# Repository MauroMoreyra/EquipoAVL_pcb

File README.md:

# EquipoAVL_pcb - vRaptor

## Guía rápida para manejo de versiones

- Habilitar modulo GitFlow en GitKraken.
- Creación de nueva versión: estando posicionado en rama "develop" o "master", GitFlow > Start Release > Nombre "vX.X" (número de versión).
- Finalización de nueva versión: GitFlow > Finish release, tildando "Delete branch". De esta forma se vuelcan a las ramas "develop" y "master" los cambios de la versión del release. A su vez se genera un TAG con el nombre del release "vX.X", que quedará de referencia histórica para futura consulta.

## Mejoras pendientes (previa validación) - vRaptor v1.2

- PCB 4 capas.
- Componentes en ambas caras.
- Revisar tamaño huellas, encapsulados.
- Modificar huellas para que posean el área que las delimita, así se valida el ERC en forma integral (con todos los checks activados).
- Ver otros errores del ERC integral.
- Verificar diseño 1.1 y corregir errores en caso de que existan.
- Verificar margenes tolerados por fabricantes, con el fin de achicar tamaños pistas y separación entre las mismas.
- Agregar información a componentes (desde esquemático).
- Poner conector DB15 en PCB, para utilizar así un cable VGA-DB15 directamente hacia la consola. Revisar tema gabinete.
- Capacitor C504 modificar para que sea de menor tamaño, reducir capacidad? low profile? investigar. Es muy alto (25mm).
- Revisar margenes laterales por tema gabinete - guia para su inserción. Revisar componentes situados muy sobre los bordes.
- Footprints IPC compatible: Revisar normativa IPC 7351 referente a los footprints recomendados de los componentes, ya que no es aconsejable utilizar los footprints recomendados por los fabricantes de las partes (se puede observar que para un mismo encapsulado, distintos fabricantes recomiendan footprints distintos, aunque varíen muy levemente). Revisar generador de footprints que sigue normativa IPC: https://www.pcblibraries.com/ a través del Library Expert.
- Footprints IPC compatible: Revisar densidad de componentes. Esto define el keepout del footprint, o sea, la distancia minima de separación con otro componente. Se recomienda usar una densidad "Normal" según el Library Expert.
- Revisar Bottom Paste de componentes de potencia (ej: LD1085), ya que IPC recomienda una "huella" de pasta de estaño con características especiales (tipo grilla, vías o microvías de disipación en cierta ubicación, etc.).

## Historial de versiones

**Versión 1.1**
- [Referencias de diseño](https://github.com/MauroMoreyra/EquipoAVL_pcb/blob/release/vRaptor-v1.1/Referencias%20de%20dise%C3%B1o%20v1.1.md).
- Se corrige el acceso de las pistas a los pads de los componentes, ahora lo hacen a 90° (no en diagonal). También, en caso de que a un pad entre y salga una pista, ahora ambas lo hacen con el mismo grosor (regla de diseño: ancho pista menor ancho pad, ya que facilita así el soldado de los componentes al no haber tanta transferencia térmica sobre las pistas).
- Se redimensiona el ancho de pistas, muchas se angostaron.
- Se modifican huellas de componentes QFN (```MPU-6050``` y ```NAU8814```), ahora tienen pads más largos (1.5mm) para facilitar el soldado manual (ese es el ancho de la    superficie del pad que la punta del soldador debe hacer contacto -punta ```900m-t-2c``` preferentemente).
- Se agrega tira de pines sobre conexiones de ```MPU-6050``` para tener como alternativa la posiblidad de colocar placa arduino de ese componente (inserción más fácil).

**Versión 1.0**
- Primera versión, entregable de materia Diseño de PCB.

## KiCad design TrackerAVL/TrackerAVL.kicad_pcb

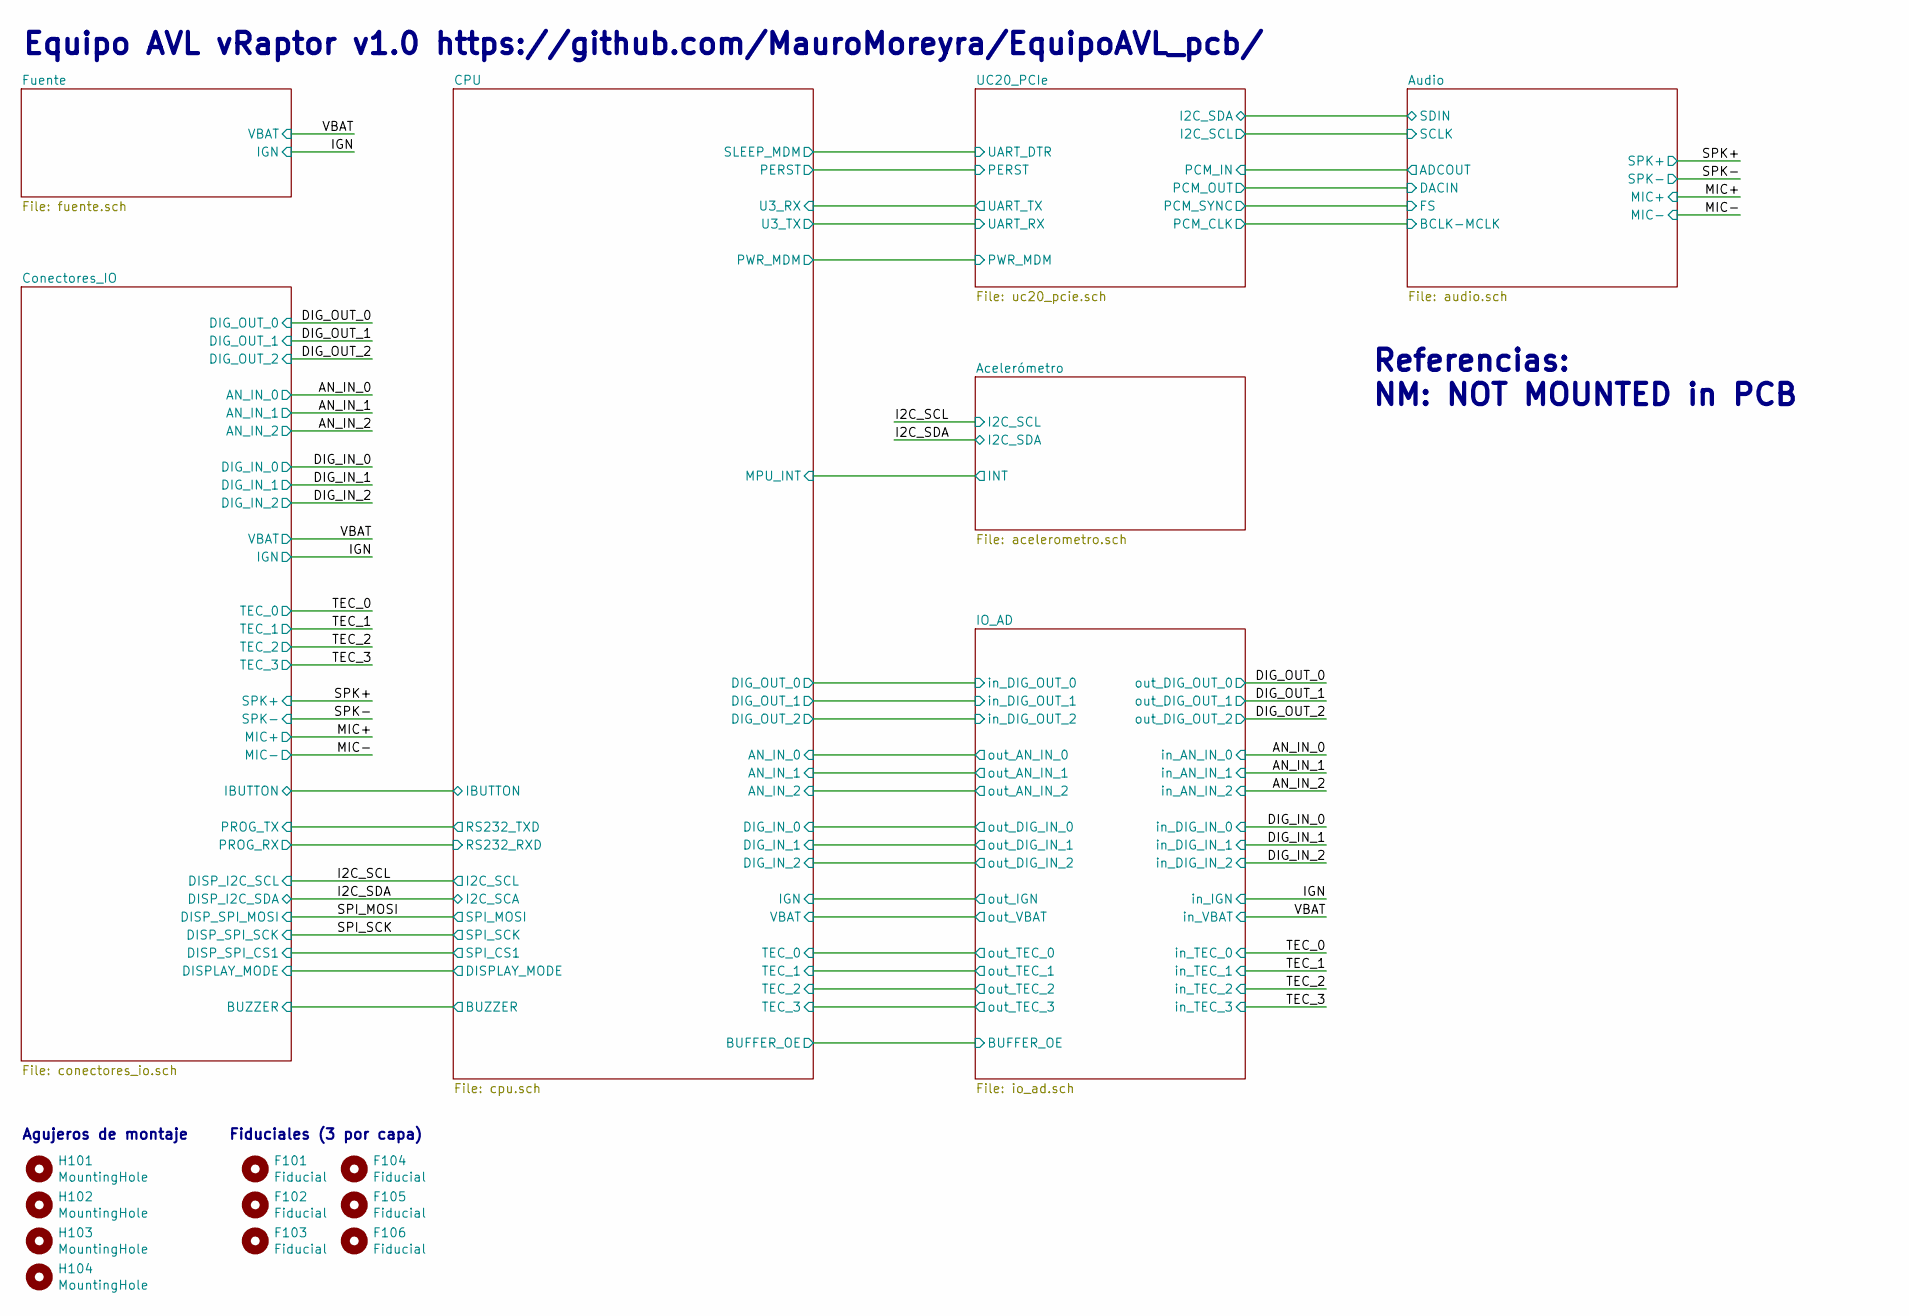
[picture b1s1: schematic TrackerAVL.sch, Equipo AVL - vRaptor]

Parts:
F101, F102, F103, F104, F105, F106: Fiducial; Fiducial_1mm_Dia_2mm_Outer
H101, H102, H103, H104: MountingHole; MountingHole_3.2mm_M3_Pad_Thin

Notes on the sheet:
Equipo AVL vRaptor v1.0 https://github.com/MauroMoreyra/EquipoAVL_pcb/
Referencias: NM: NOT MOUNTED in PCB
Agujeros de montaje
Fiduciales (3 por capa)

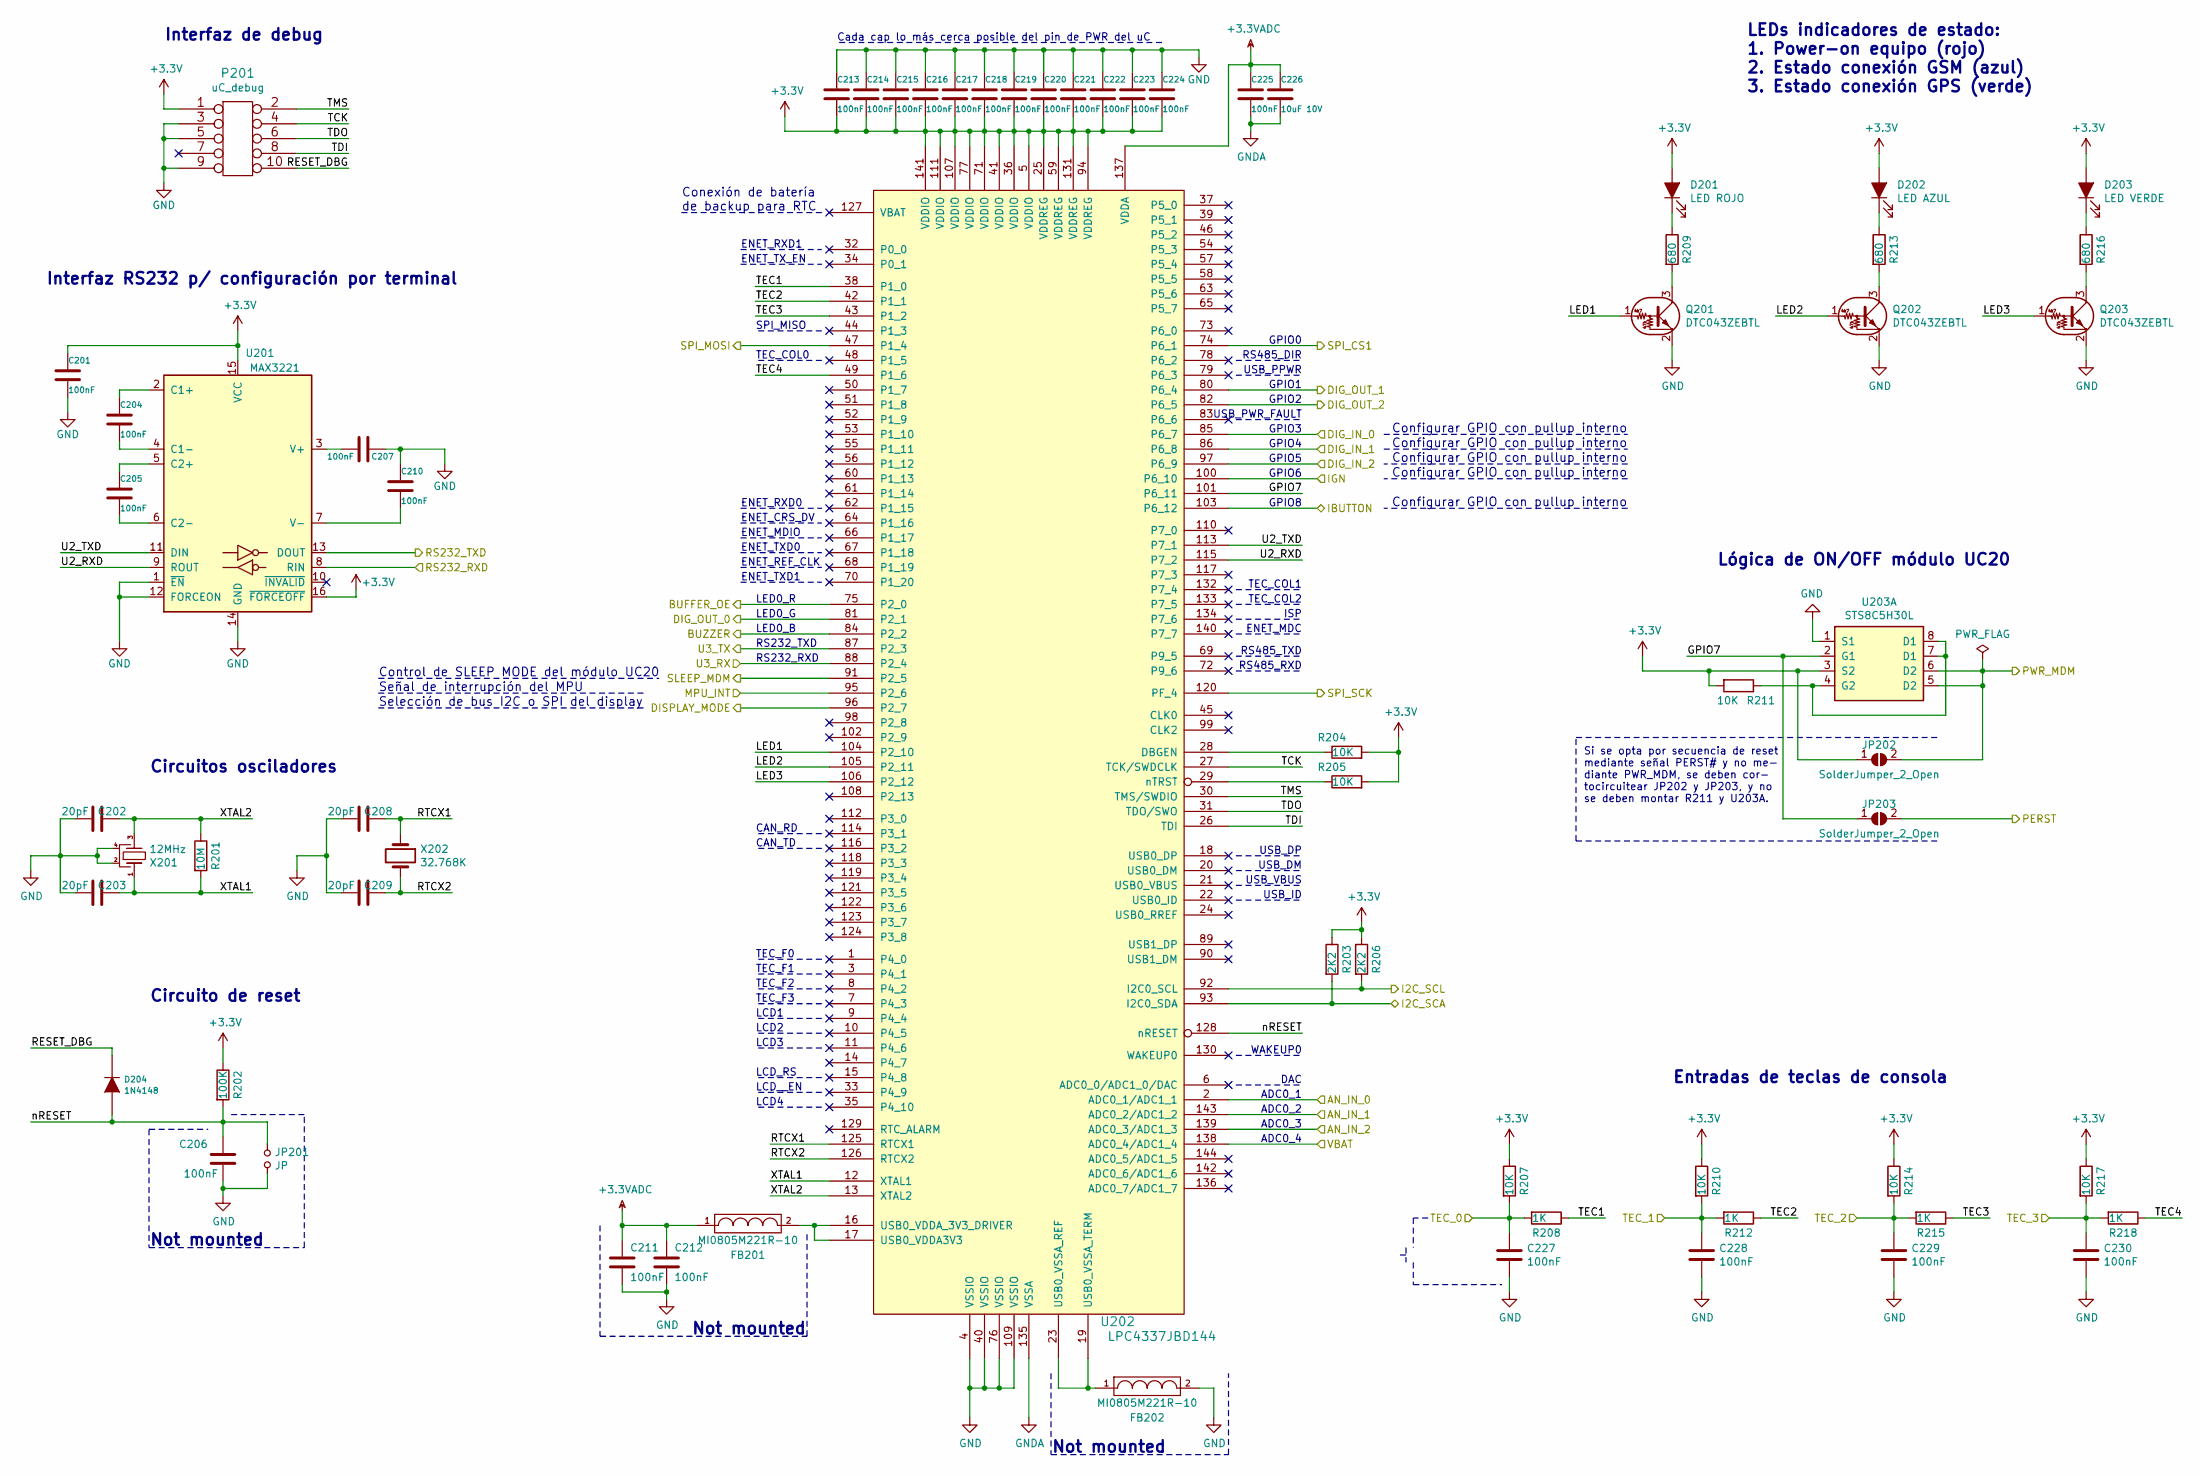
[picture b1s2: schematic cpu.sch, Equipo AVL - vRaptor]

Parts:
C201, C204, C205, C206, C207, C210, C211, C212, C213, C214, C215, C216, C217, C218, C219, C220, C221, C222, C223, C224, C225, C227, C228, C229, C230: 100nF; C_0805_2012Metric_Pad1.15x1.40mm_HandSolder
C202, C203, C208, C209: 20pF; C_0805_2012Metric_Pad1.15x1.40mm_HandSolder
C226: 10uF 10V; C_1206_3216Metric_Pad1.42x1.75mm_HandSolder
D201: LED ROJO; LED_0805_2012Metric_Pad1.15x1.40mm_HandSolder
D202: LED AZUL; LED_0805_2012Metric_Pad1.15x1.40mm_HandSolder
D203: LED VERDE; LED_0805_2012Metric_Pad1.15x1.40mm_HandSolder
D204: 1N4148; D_SOD-123
FB201, FB202: MI0805M221R-10; L_0805_2012Metric_Pad1.15x1.40mm_HandSolder
JP201: JP; PinHeader_1x02_P2.54mm_Vertical
JP202, JP203: SolderJumper_2_Open; SolderJumper-2_P1.3mm_Open_Pad1.0x1.5mm
P201: uC_debug; Pin_Array_5x2_1.27mm_SMD
Q201, Q202, Q203: DTC043ZEBTL; SOT-523_(SOT-416)
R201: 10M; R_0805_2012Metric_Pad1.15x1.40mm_HandSolder
R202: 100K; R_0805_2012Metric_Pad1.15x1.40mm_HandSolder
R203, R206: 2K2; R_0805_2012Metric_Pad1.15x1.40mm_HandSolder
R204, R205, R207, R210, R211, R214, R217: 10K; R_0805_2012Metric_Pad1.15x1.40mm_HandSolder
R208, R212, R215, R218: 1K; R_0805_2012Metric_Pad1.15x1.40mm_HandSolder
R209, R213, R216: 680; R_0805_2012Metric_Pad1.15x1.40mm_HandSolder
U201: MAX3221; SSOP-16_5.3x6.2mm_P0.65mm
U202: LPC4337JBD144; LQFP144-M05
U203: STS8C5H30L; SOIC-8_3.9x4.9mm_P1.27mm
X201: 12MHz; FA238V-XTAL; Digikey/Mouser 887-1831-1-ND
X202: 32.768K; 32.768-XTAL-SMD

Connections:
+3.3VADC: C211.1, C212.1, C225.1, C226.1, FB201.1, U202.137 (VDDA); also elsewhere on the board
+3V3: C201.1, C213.2, C214.2, C215.2, C216.2, C217.2, C218.2, C219.2, C220.2, C221.2, C222.2, C223.2, C224.2, D201.2 (A), D202.2 (A), D203.2 (A), JP202.1 (A), P201.1, R202.1, R203.1, R204.2, R205.2, R206.1, R207.1, R210.1, R211.2, R214.1, R217.1, U201.15 (VCC), U201.16 (~FORCEOFF), U202.5 (VDDIO), U202.25 (VDDREG), U202.36 (VDDIO), U202.41 (VDDIO), U202.59 (VDDREG), U202.71 (VDDIO), U202.77 (VDDIO), U202.94 (VDDREG), U202.107 (VDDIO), U202.111 (VDDIO), U202.131 (VDDREG), U202.141 (VDDIO), U203.3 (S2); also elsewhere on the board
/Acelerómetro/INT: U202.95 (P2_6); also elsewhere on the board
/CPU/AN_IN_0: U202.2 (ADC0_1/ADC1_1); also elsewhere on the board
/CPU/AN_IN_1: U202.143 (ADC0_2/ADC1_2); also elsewhere on the board
/CPU/AN_IN_2: U202.139 (ADC0_3/ADC1_3); also elsewhere on the board
/CPU/BUFFER_OE: U202.75 (P2_0); also elsewhere on the board
/CPU/BUZZER: U202.84 (P2_2); also elsewhere on the board
/CPU/DIG_IN_0: U202.85 (P6_7); also elsewhere on the board
/CPU/DIG_IN_1: U202.86 (P6_8); also elsewhere on the board
/CPU/DIG_IN_2: U202.97 (P6_9); also elsewhere on the board
/CPU/DIG_OUT_0: U202.81 (P2_1); also elsewhere on the board
/CPU/DIG_OUT_1: U202.80 (P6_4); also elsewhere on the board
/CPU/DIG_OUT_2: U202.82 (P6_5); also elsewhere on the board
/CPU/DISPLAY_MODE: U202.96 (P2_7); also elsewhere on the board
/CPU/GPIO7: JP203.1 (A), U202.101 (P6_11), U203.2 (G1)
/CPU/IBUTTON: U202.103 (P6_12); also elsewhere on the board
/CPU/IGN: U202.100 (P6_10); also elsewhere on the board
/CPU/LED1: Q201.1 (B), U202.104 (P2_10)
/CPU/LED2: Q202.1 (B), U202.105 (P2_11)
/CPU/LED3: Q203.1 (B), U202.106 (P2_12)
/CPU/PERST: JP203.2 (B); also elsewhere on the board
/CPU/PWR_MDM: JP202.2 (B), U203.5 (D2), U203.6 (D2); also elsewhere on the board
/CPU/RESET_DBG: D204.2 (K), P201.10
/CPU/RTCX1: C208.1, U202.125 (RTCX1), X202.1
/CPU/RTCX2: C209.1, U202.126 (RTCX2), X202.2
/CPU/SLEEP_MDM: U202.91 (P2_5); also elsewhere on the board
/CPU/TCK: P201.4, U202.27 (TCK/SWDCLK)
/CPU/TDI: P201.8, U202.26 (TDI)
/CPU/TDO: P201.6, U202.31 (TDO/SWO)
/CPU/TEC1: R208.1, U202.38 (P1_0)
/CPU/TEC2: R212.1, U202.42 (P1_1)
/CPU/TEC3: R215.1, U202.43 (P1_2)
/CPU/TEC4: R218.1, U202.49 (P1_6)
/CPU/TEC_0: C227.1, R207.2, R208.2; also elsewhere on the board
/CPU/TEC_1: C228.1, R210.2, R212.2; also elsewhere on the board
/CPU/TEC_2: C229.1, R214.2, R215.2; also elsewhere on the board
/CPU/TEC_3: C230.1, R217.2, R218.2; also elsewhere on the board
/CPU/TMS: P201.2, U202.30 (TMS/SWDIO)
/CPU/U2_RXD: U201.9 (ROUT), U202.115 (P7_2)
/CPU/U2_TXD: U201.11 (DIN), U202.113 (P7_1)
/CPU/U3_RX: U202.88 (P2_4); also elsewhere on the board
/CPU/U3_TX: U202.87 (P2_3); also elsewhere on the board
/CPU/VBAT: U202.138 (ADC0_4/ADC1_4); also elsewhere on the board
/CPU/XTAL1: C203.1, R201.2, U202.12 (XTAL1), X201.1 (A)
/CPU/XTAL2: C202.1, R201.1, U202.13 (XTAL2), X201.3 (B)
/CPU/nRESET: C206.1, D204.1 (A), JP201.1, R202.2, U202.128 (nRESET)
/Conectores_IO/DISP_SPI_CS1: U202.74 (P6_1); also elsewhere on the board
/Conectores_IO/PROG_RX: U201.8 (RIN); also elsewhere on the board
/Conectores_IO/PROG_TX: U201.13 (DOUT); also elsewhere on the board
/I2C_SCL: R206.2, U202.92 (I2C0_SCL); also elsewhere on the board
/I2C_SDA: R203.2, U202.93 (I2C0_SDA); also elsewhere on the board
/SPI_MOSI: U202.47 (P1_4); also elsewhere on the board
/SPI_SCK: U202.120 (PF_4); also elsewhere on the board
GND: C201.2, C202.2, C203.2, C206.2, C207.1, C208.2, C209.2, C210.1, C211.2, C212.2, C213.1, C214.1, C215.1, C216.1, C217.1, C218.1, C219.1, C220.1, C221.1, C222.1, C223.1, C224.1, C227.2, C228.2, C229.2, C230.2, FB202.2, JP201.2, P201.3, P201.5, P201.9, Q201.2 (E), Q202.2 (E), Q203.2 (E), U201.1 (~EN), U201.12 (FORCEON), U201.14 (GND), U202.4 (VSSIO), U202.40 (VSSIO), U202.76 (VSSIO), U202.109 (VSSIO), U203.1 (S1), X201.2 (GND), X201.4 (GND); also elsewhere on the board
GNDA: C225.2, C226.2, U202.135 (VSSA); also elsewhere on the board
unnamed: C204.1, U201.2 (C1+)
unnamed: C204.2, U201.4 (C1-)
unnamed: C205.1, U201.5 (C2+)
unnamed: C205.2, U201.6 (C2-)
unnamed: C207.2, U201.3 (V+)
unnamed: C210.2, U201.7 (V-)
unnamed: D201.1 (K), R209.1
unnamed: D202.1 (K), R213.1
unnamed: D203.1 (K), R216.1
unnamed: FB201.2, U202.16 (USB0_VDDA_3V3_DRIVER), U202.17 (USB0_VDDA3V3)
unnamed: FB202.1, U202.19 (USB0_VSSA_TERM), U202.23 (USB0_VSSA_REF)
unnamed: Q201.3 (C), R209.2
unnamed: Q202.3 (C), R213.2
unnamed: Q203.3 (C), R216.2
unnamed: R204.1, U202.28 (DBGEN)
unnamed: R205.1, U202.29 (nTRST)
unnamed: R211.1, U203.4 (G2), U203.7 (D1), U203.8 (VSS)

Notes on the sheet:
Configurar GPIO con pullup interno
LEDs indicadores de estado: 1. Power-on equipo (rojo) 2. Estado conexión GSM (azul) 3. Estado conexión GPS (verde)
Entradas de teclas de consola
WAKEUP0
USB_PWR_FAULT
USB_PPWR
RS485_DIR
TEC_COL2
TEC_COL1
CAN_RD
CAN_TD
TEC_F0
TEC_F1
TEC_F2
TEC_F3
LCD1
LCD2
LCD3
LCD_RS
LCD__EN
LCD4
Circuitos osciladores
Not mounted
ENET_TXD1
ENET_REF_CLK
ENET_TXD0
ENET_MDIO
ENET_CRS_DV
ENET_RXD0
TEC_COL0
ENET_TX_EN
ENET_RXD1
Conexión de batería de backup para RTC
ENET_MDC
ISP
RS485_TXD
RS485_RXD
Interfaz de debug
DAC
Circuito de reset

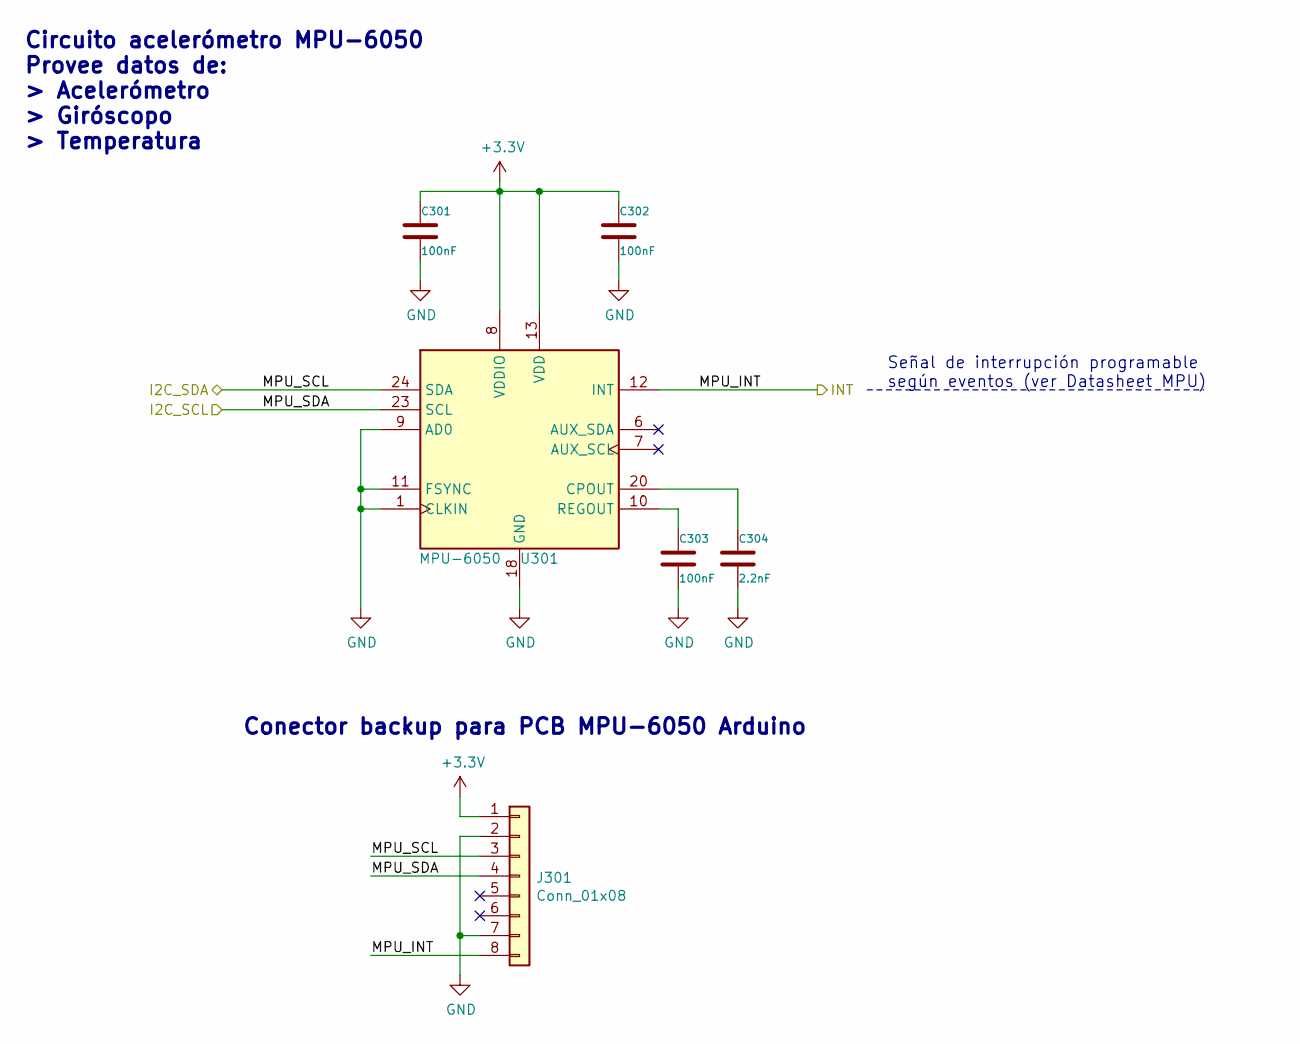
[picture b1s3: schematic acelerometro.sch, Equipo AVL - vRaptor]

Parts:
C301, C302, C303: 100nF; C_0805_2012Metric_Pad1.15x1.40mm_HandSolder
C304: 2.2nF; C_0805_2012Metric_Pad1.15x1.40mm_HandSolder
J301: Conn_01x08; PinHeader_1x08_P2.54mm_Vertical
U301: MPU-6050; InvenSense_QFN-24_4x4mm_P0.5mm_HandSoldering

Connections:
+3V3: C301.1, C302.1, J301.1, U301.8 (VDDIO), U301.13 (VDD); also elsewhere on the board
/Acelerómetro/INT: J301.8, U301.12 (INT); also elsewhere on the board
/I2C_SCL: J301.4, U301.23 (SCL); also elsewhere on the board
/I2C_SDA: J301.3, U301.24 (SDA); also elsewhere on the board
GND: C301.2, C302.2, C303.2, C304.2, J301.2, J301.7, U301.1 (CLKIN), U301.9 (AD0), U301.11 (FSYNC), U301.18 (GND); also elsewhere on the board
unnamed: C303.1, U301.10 (REGOUT)
unnamed: C304.1, U301.20 (CPOUT)

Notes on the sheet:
Circuito acelerómetro MPU-6050 Provee datos de: > Acelerómetro > Giróscopo > Temperatura
Señal de interrupción programable según eventos (ver Datasheet MPU)
Conector backup para PCB MPU-6050 Arduino

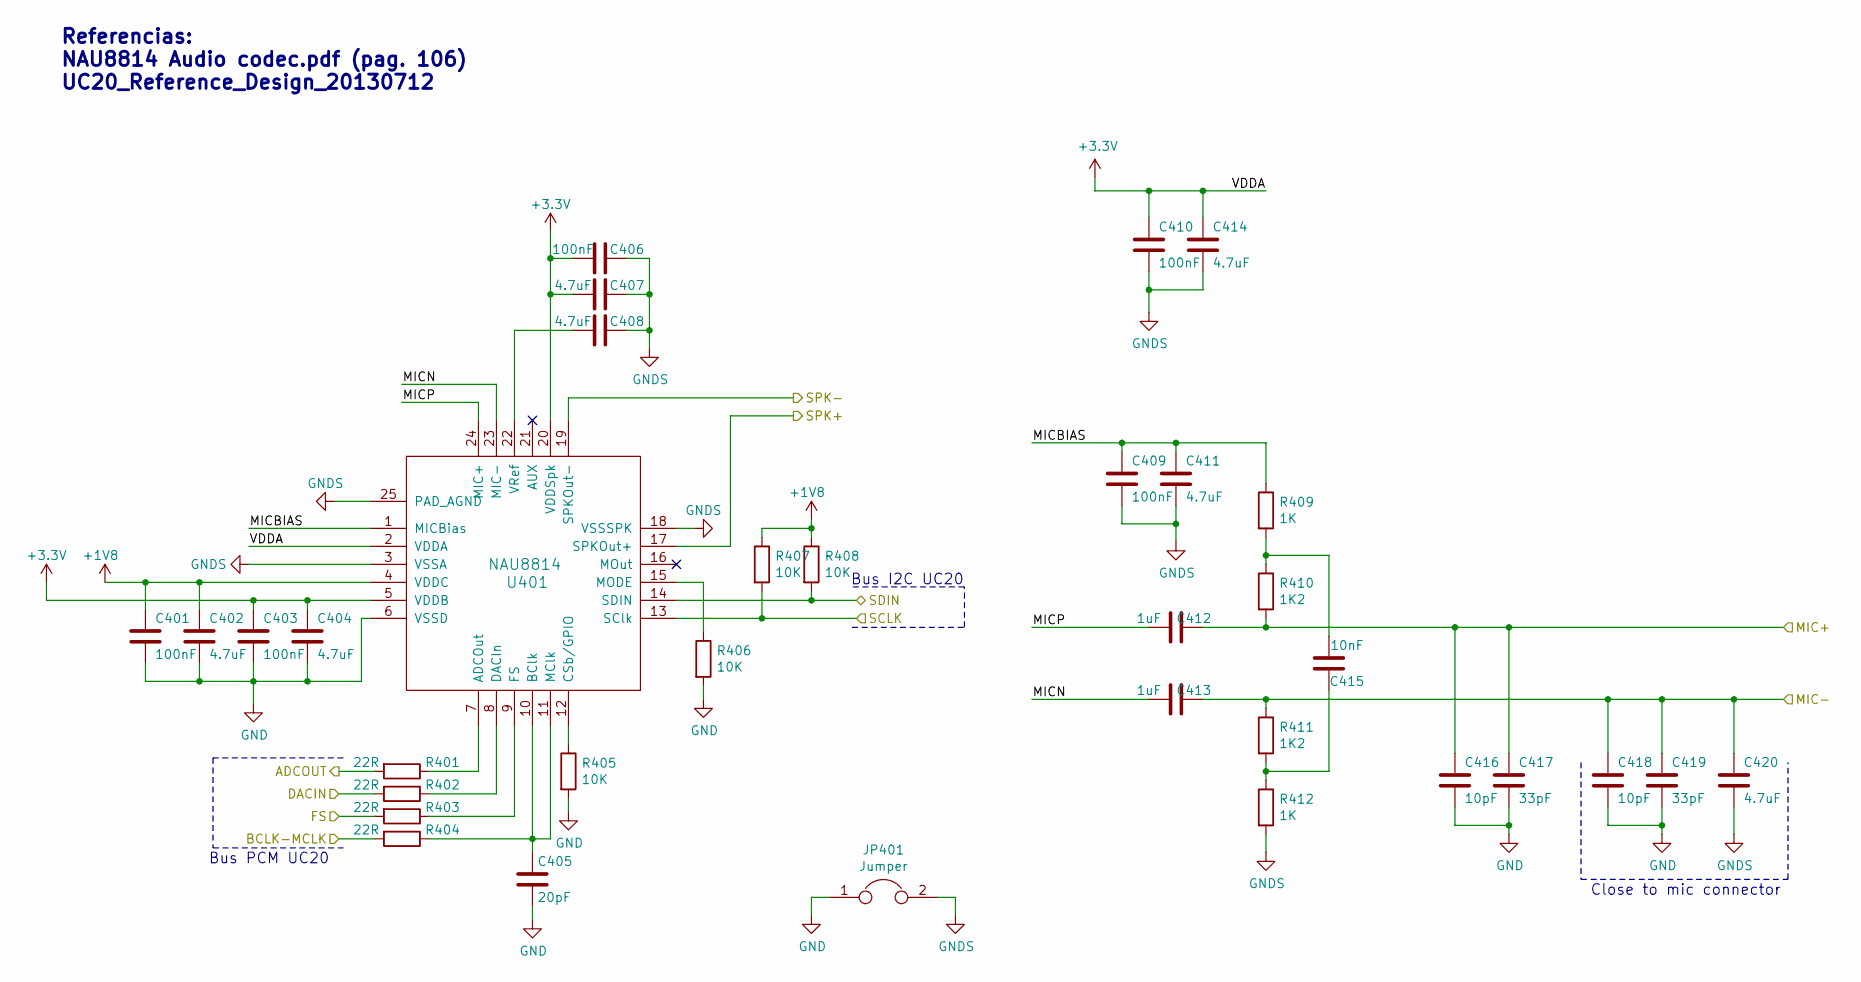
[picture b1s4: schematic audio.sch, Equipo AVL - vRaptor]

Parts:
C401, C403, C406, C409, C410: 100nF; C_0805_2012Metric_Pad1.15x1.40mm_HandSolder
C402, C404, C407, C408, C411, C414, C420: 4.7uF; C_0805_2012Metric_Pad1.15x1.40mm_HandSolder
C405: 20pF; C_0805_2012Metric_Pad1.15x1.40mm_HandSolder
C412, C413: 1uF; C_0805_2012Metric_Pad1.15x1.40mm_HandSolder
C415: 10nF; C_0805_2012Metric_Pad1.15x1.40mm_HandSolder
C416, C418: 10pF; C_0805_2012Metric_Pad1.15x1.40mm_HandSolder
C417, C419: 33pF; C_0805_2012Metric_Pad1.15x1.40mm_HandSolder
JP401: Jumper; SolderJumper-2_P1.3mm_Bridged_Pad1.0x1.5mm
R401, R402, R403, R404: 22R; R_0805_2012Metric_Pad1.15x1.40mm_HandSolder
R405, R406, R407, R408: 10K; R_0805_2012Metric_Pad1.15x1.40mm_HandSolder
R409, R412: 1K; R_0805_2012Metric_Pad1.15x1.40mm_HandSolder
R410, R411: 1K2; R_0805_2012Metric_Pad1.15x1.40mm_HandSolder
U401: NAU8814; NAU8814_QFN-24_4x4mm_Pitch0.5mm_EPAD_HandSoldering

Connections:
+1V8: C401.1, C402.1, R407.1, R408.1, U401.4 (VDDC); also elsewhere on the board
+3V3: C403.1, C404.1, C406.1, C407.1, C410.1, C414.1, U401.2 (VDDA), U401.5 (VDDB), U401.20 (VDDSpk); also elsewhere on the board
/Audio/ADCOUT: R401.2; also elsewhere on the board
/Audio/BCLK-MCLK: R404.2; also elsewhere on the board
/Audio/DACIN: R402.2; also elsewhere on the board
/Audio/FS: R403.2; also elsewhere on the board
/Audio/MICBIAS: C409.1, C411.1, R409.1, U401.1 (MICBias)
/Audio/MICN: C413.1, U401.23 (MIC-)
/Audio/MICP: C412.1, U401.24 (MIC+)
/MIC+: C412.2, C416.1, C417.1, R410.2; also elsewhere on the board
/MIC-: C413.2, C418.1, C419.1, C420.1, R411.1; also elsewhere on the board
/SPK+: U401.17 (SPKOut+); also elsewhere on the board
/SPK-: U401.19 (SPKOut-); also elsewhere on the board
/UC20_PCIe/I2C_SCL: R407.2, U401.13 (SClk); also elsewhere on the board
/UC20_PCIe/I2C_SDA: R408.2, U401.14 (SDIN); also elsewhere on the board
GND: C401.2, C402.2, C403.2, C404.2, C405.2, C416.2, C417.2, C418.2, C419.2, JP401.1, R405.2, R406.2, U401.6 (VSSD); also elsewhere on the board
GNDS: C406.2, C407.2, C408.2, C409.2, C410.2, C411.2, C414.2, C420.2, JP401.2, R412.2, U401.3 (VSSA), U401.18 (VSSSPK), U401.25 (PAD_AGND)
unnamed: C405.1, R404.1, U401.10 (BClk), U401.11 (MClk)
unnamed: C408.1, U401.22 (VRef)
unnamed: C415.1, R409.2, R410.1
unnamed: C415.2, R411.2, R412.1
unnamed: R401.1, U401.7 (ADCOut)
unnamed: R402.1, U401.8 (DACIn)
unnamed: R403.1, U401.9 (FS)
unnamed: R405.1, U401.12 (CSb/GPIO)
unnamed: R406.1, U401.15 (MODE)

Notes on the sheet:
Referencias: NAU8814 Audio codec.pdf (pag. 106) UC20_Reference_Design_20130712
Close to mic connector
Bus I2C UC20
Bus PCM UC20

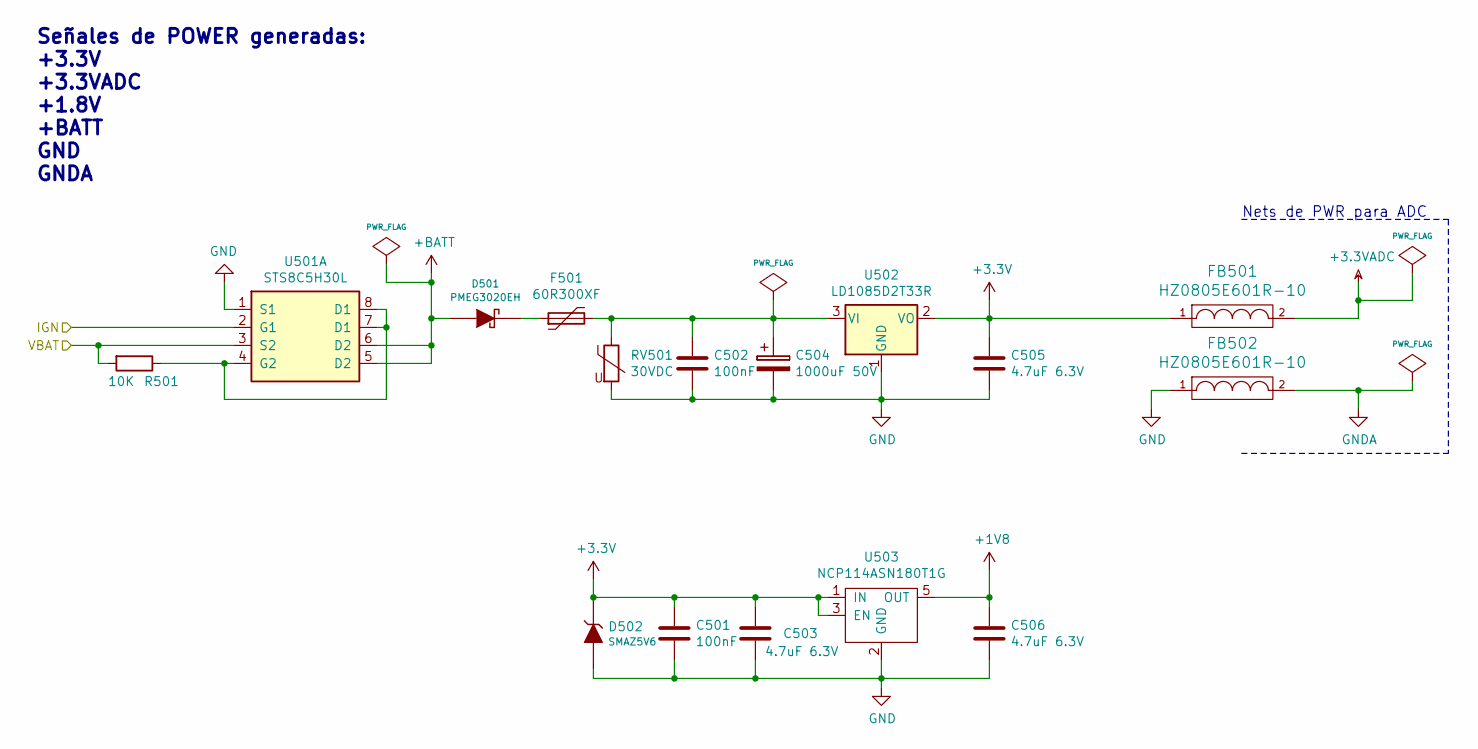
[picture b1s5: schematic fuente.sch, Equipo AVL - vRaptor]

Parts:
C501, C502: 100nF; C_0805_2012Metric_Pad1.15x1.40mm_HandSolder
C503, C505, C506: 4.7uF 6.3V; C_0805_2012Metric_Pad1.15x1.40mm_HandSolder
C504: 1000uF 50V; CP_Radial_D12.5mm_P5.00mm
D501: PMEG3020EH; D_SOD-123F
D502: SMAZ5V6; DO-214AC (SMA)
F501: 60R300XF
FB501, FB502: HZ0805E601R-10; L_0805_2012Metric_Pad1.15x1.40mm_HandSolder
R501: 10K; R_0805_2012Metric_Pad1.15x1.40mm_HandSolder
RV501: 30VDC; D_1206_3216Metric_Pad1.42x1.75mm_HandSolder
U501: STS8C5H30L; SOIC-8_3.9x4.9mm_P1.27mm
U502: LD1085D2T33R; TO-263-3_TabPin2
U503: NCP114ASN180T1G; TSOP-5_NCP114

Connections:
+1V8: C506.1, U503.5 (OUT); also elsewhere on the board
+3.3VADC: FB501.2; also elsewhere on the board
+3V3: C501.1, C503.1, C505.1, D502.2 (K), FB501.1, U502.2 (VO), U503.1 (IN), U503.3 (EN); also elsewhere on the board
+BATT: D501.1 (A), U501.5 (D2), U501.6 (D2)
/IGN: U501.2 (G1); also elsewhere on the board
/VBAT: R501.2, U501.3 (S2); also elsewhere on the board
GND: C501.2, C502.2, C503.2, C504.2, C505.2, C506.2, D502.1 (A), FB502.1, RV501.2, U501.1 (S1), U502.1 (GND), U503.2 (GND); also elsewhere on the board
GNDA: FB502.2; also elsewhere on the board
unnamed: C502.1, C504.1, F501.2, RV501.1, U502.3 (VI)
unnamed: D501.2 (K), F501.1
unnamed: R501.1, U501.4 (G2), U501.7 (D1), U501.8 (VSS)

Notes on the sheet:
Nets de PWR para ADC
Señales de POWER generadas: +3.3V +3.3VADC +1.8V +BATT GND GNDA

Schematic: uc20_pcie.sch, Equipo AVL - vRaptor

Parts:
R601, R602, R603: 10K; R_0805_2012Metric_Pad1.15x1.40mm_HandSolder
U601: MPCIE-Socket; mpcie-socket-latch

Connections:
+1V8: R602.1, R603.1; also elsewhere on the board
+3V3: R601.1; also elsewhere on the board
/Audio/ADCOUT: U601.49; also elsewhere on the board
/Audio/BCLK-MCLK: U601.45; also elsewhere on the board
/Audio/DACIN: U601.47; also elsewhere on the board
/Audio/FS: U601.51; also elsewhere on the board
/CPU/PERST: U601.22; also elsewhere on the board
/CPU/PWR_MDM: U601.2, U601.39, U601.41, U601.52; also elsewhere on the board
/CPU/SLEEP_MDM: U601.31; also elsewhere on the board
/CPU/U3_RX: U601.13; also elsewhere on the board
/CPU/U3_TX: U601.11; also elsewhere on the board
/UC20_PCIe/I2C_SCL: R603.2, U601.30; also elsewhere on the board
/UC20_PCIe/I2C_SDA: R602.2, U601.32; also elsewhere on the board
/UC20_PCIe/W_DISABLE: R601.2, U601.20
GND: U601.4, U601.9, U601.15, U601.18, U601.21, U601.26, U601.27, U601.29, U601.34, U601.35, U601.37, U601.40, U601.43, U601.50; also elsewhere on the board

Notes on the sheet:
Control de "SLEEP MODE"
Audio driver
Comunicación serial
Pull-ups +3.3V
Pull-ups +1.8V
Señales de control
SIM Holder ya está sobre el módulo UC20, por lo tanto estas salidas no se conectan
Señal para despertar al uC (no usado)

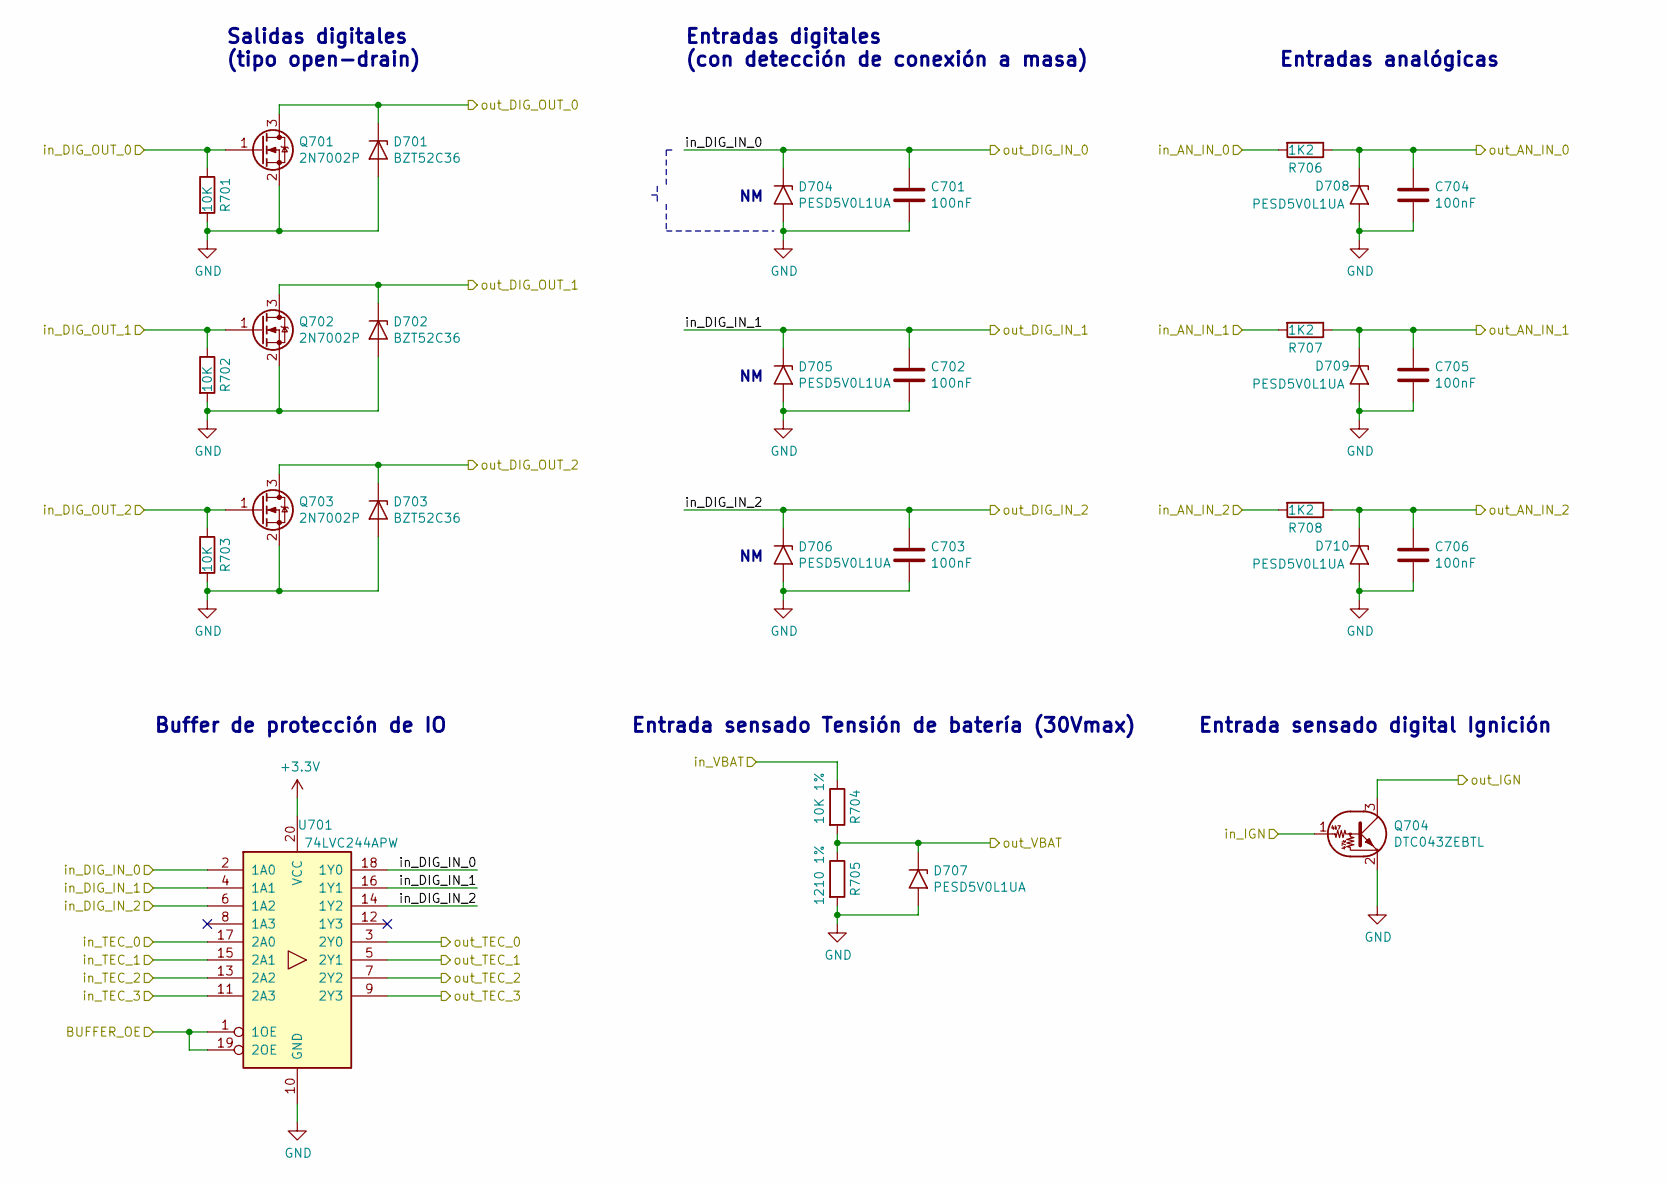
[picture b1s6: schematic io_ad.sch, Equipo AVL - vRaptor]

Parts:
C701, C702, C703, C704, C705, C706: 100nF; C_0805_2012Metric_Pad1.15x1.40mm_HandSolder
D701, D702, D703: BZT52C36; D_SOD-123
D704, D705, D706, D707, D708, D709, D710: PESD5V0L1UA; D_SOD-323_HandSoldering
Q701, Q702, Q703: 2N7002P; SOT-23_Handsoldering
Q704: DTC043ZEBTL; SOT-523_(SOT-416)
R701, R702, R703: 10K; R_0805_2012Metric_Pad1.15x1.40mm_HandSolder
R704: 10K 1%; R_0805_2012Metric_Pad1.15x1.40mm_HandSolder
R705: 1210 1%; R_0805_2012Metric_Pad1.15x1.40mm_HandSolder
R706, R707, R708: 1K2; R_0805_2012Metric_Pad1.15x1.40mm_HandSolder
U701: 74LVC244APW; TSSOP-20_4.4x6.5mm_P0.65mm

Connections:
+3V3: U701.20 (VCC); also elsewhere on the board
/AN_IN_0: R706.2; also elsewhere on the board
/AN_IN_1: R707.2; also elsewhere on the board
/AN_IN_2: R708.2; also elsewhere on the board
/CPU/AN_IN_0: C704.1, D708.1 (A1), R706.1; also elsewhere on the board
/CPU/AN_IN_1: C705.1, D709.1 (A1), R707.1; also elsewhere on the board
/CPU/AN_IN_2: C706.1, D710.1 (A1), R708.1; also elsewhere on the board
/CPU/BUFFER_OE: U701.1 (1OE), U701.19 (2OE); also elsewhere on the board
/CPU/DIG_IN_0: C701.1, D704.1 (A1), U701.18 (1Y0); also elsewhere on the board
/CPU/DIG_IN_1: C702.1, D705.1 (A1), U701.16 (1Y1); also elsewhere on the board
/CPU/DIG_IN_2: C703.1, D706.1 (A1), U701.14 (1Y2); also elsewhere on the board
/CPU/DIG_OUT_0: Q701.1 (G), R701.1; also elsewhere on the board
/CPU/DIG_OUT_1: Q702.1 (G), R702.1; also elsewhere on the board
/CPU/DIG_OUT_2: Q703.1 (G), R703.1; also elsewhere on the board
/CPU/IGN: Q704.3 (C); also elsewhere on the board
/CPU/TEC_0: U701.3 (2Y0); also elsewhere on the board
/CPU/TEC_1: U701.5 (2Y1); also elsewhere on the board
/CPU/TEC_2: U701.7 (2Y2); also elsewhere on the board
/CPU/TEC_3: U701.9 (2Y3); also elsewhere on the board
/CPU/VBAT: D707.1 (A1), R704.2, R705.1; also elsewhere on the board
/DIG_IN_0: U701.2 (1A0); also elsewhere on the board
/DIG_IN_1: U701.4 (1A1); also elsewhere on the board
/DIG_IN_2: U701.6 (1A2); also elsewhere on the board
/DIG_OUT_0: D701.1 (K), Q701.3 (D); also elsewhere on the board
/DIG_OUT_1: D702.1 (K), Q702.3 (D); also elsewhere on the board
/DIG_OUT_2: D703.1 (K), Q703.3 (D); also elsewhere on the board
/IGN: Q704.1 (B); also elsewhere on the board
/TEC_0: U701.17 (2A0); also elsewhere on the board
/TEC_1: U701.15 (2A1); also elsewhere on the board
/TEC_2: U701.13 (2A2); also elsewhere on the board
/TEC_3: U701.11 (2A3); also elsewhere on the board
/VBAT: R704.1; also elsewhere on the board
GND: C701.2, C702.2, C703.2, C704.2, C705.2, C706.2, D701.2 (A), D702.2 (A), D703.2 (A), D704.2 (A2), D705.2 (A2), D706.2 (A2), D707.2 (A2), D708.2 (A2), D709.2 (A2), D710.2 (A2), Q701.2 (S), Q702.2 (S), Q703.2 (S), Q704.2 (E), R701.2, R702.2, R703.2, R705.2, U701.10 (GND); also elsewhere on the board

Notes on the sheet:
Salidas digitales (tipo open-drain)
Entradas digitales (con detección de conexión a masa)
Entradas analógicas
Entrada sensado Tensión de batería (30Vmax)
Entrada sensado digital Ignición
Buffer de protección de IO
